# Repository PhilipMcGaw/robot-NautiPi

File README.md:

# robot-NautiPi

NautiPi is the physical hardware and embedded-project repository for the robot projects. It contains electronics, PCB and KiCad work, Arduino projects, component records, mechanical references, photographs, and retained historical hardware material.

## Robots project

Cross-project architecture, engineering rationale, significant decisions, reusable guidance, and the overall roadmap are maintained in [Chartroom](https://chartroom.philipmcgaw.com/).

NautiPi works alongside the other current project repositories:

- [Chartroom](https://chartroom.philipmcgaw.com/) — central engineering knowledge base and cross-project documentation.
- [CuttleOS](https://github.com/PhilipMcGaw/robot-CuttleOS) — robot-side software, including Cockpit, Control, and Datalogger.
- [SquidLink](https://github.com/PhilipMcGaw/robot-SquidLink) — independent ROS 2/Gazebo simulation and integration-test environment.

The repositories are separate and connected by documented interfaces. NautiPi is the source of truth for the physical hardware design record; it is not the source of truth for software implementation or simulation behaviour. Chartroom records the cross-project engineering context.

The cross-repository system architecture is maintained in [Chartroom](https://chartroom.philipmcgaw.com/). NautiPi-specific physical hardware architecture is defined in [`docs/hardware-architecture.md`](docs/hardware-architecture.md).

## Documentation standard

Project-wide documentation conventions are defined by the [Robots Project Documentation Standard](https://chartroom.philipmcgaw.com/development/documentation-standard/), maintained in Chartroom. NautiPi follows that standard and does not maintain a separate copy of the project-wide documentation rules.

## Repository layout

### ROV hardware

- [`ROV - Conductivity Temperature and Depth Transducer/`](<ROV - Conductivity Temperature and Depth Transducer/README.md>) — conductivity, temperature, and depth transducer design and embedded-project material.
- [`ROV - Light Module/`](<ROV - Light Module/README.md>) — ROV lighting electronics and embedded-project material.
- [`ROV - Main Body/`](<ROV - Main Body/README.md>) — main-body hardware archive, including PCB designs, component records, mechanical references, and historical integration material.
- [`ROV - Navigator/`](<ROV - Navigator/README.md>) — Navigator PCB, schematics, power management, status LED, leak detection, and shared KiCad resources.

### K9 hardware

- [`K9 - Main Body/`](<K9 - Main Body/README.md>) — K9 main-body hardware designs, body-control modules, motor-driver material, and project references.

### Testbot hardware

- [`TestBot - Main Body/`](<TestBot - Main Body/README.md>) — physical Testbot CAD, wiring, build notes, photographs, and validation evidence.

### MarsBot hardware and research

- [`MarsBot - Main Body/`](<MarsBot - Main Body/README.md>) — retained MarsBot main-body material and long-horizon rover-development research and roadmap work.

### Other retained material

- [`Remote Sensors/`](<Remote Sensors/README.md>) — retained remote-sensor project material.
- [`Traffic Light/`](<Traffic Light/README.md>) — historical traffic-light project photographs and reference material.

## Current status

NautiPi contains a mixture of current design work, development material, and historical project records. The presence of a design file, firmware, photograph, or other project artefact does not establish that the associated hardware is currently manufactured, assembled, commissioned, calibrated, or integrated.

Hardware assembly, electrical commissioning, calibration, environmental testing, and robot integration are separate engineering activities and require their own evidence.

The ROV hardware projects are not currently represented as production-validated by this repository unless explicit validation evidence is recorded.

## Relationship to software and simulation

CuttleOS is the current software architecture and runtime boundary. SquidLink is the current simulation and integration-test boundary. Historical software notes retained in NautiPi must not be treated as authoritative when they conflict with those repositories.

Hardware references in NautiPi do not, by themselves, authorise a Control allocation, GPIO assignment, RS-485 mapping, or production wiring arrangement. Such allocations must be established by the current engineering and software interface documentation.

## Documentation

For cross-project documentation and engineering rationale, see [Chartroom](https://chartroom.philipmcgaw.com/).

Each substantial hardware project should have a local `README.md` describing its purpose, contents, current status, and relationship to the wider system.

## People who have helped

- Philip 'Skippy' McGaw - <philip@mcgaw.eu> - [philipmcgaw.com](https://philipmcgaw.com)
- Tamarisk 'NotQuiteHere' McGaw - <tamarisk@mcgaw.eu> - [tamarisk.it](https://tamarisk.it)
- Bob 'thinkl33t' Clough - <bob@clough.me> - [thinkl33t.co.uk](https://thinkl33t.co.uk)

## Licence

The repository uses separate licences for project software and documentation, and for hardware design material. See [`LICENSES.md`](LICENSES.md) for the authoritative licensing map and the complete licence texts.

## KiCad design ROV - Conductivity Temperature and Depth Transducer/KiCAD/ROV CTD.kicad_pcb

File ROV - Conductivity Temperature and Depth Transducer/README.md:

# ROV Conductivity, Temperature, and Depth Transducer

This folder contains the KiCad design files, reference material, and embedded-project material for the ROV conductivity, temperature, and depth transducer.

## Contents

- `KiCAD/` — schematics, PCB layouts, project files, generated documents, and component resources.
- `Software/` — Arduino and PlatformIO firmware experiments and supporting libraries.

## Interface baseline

The shared node design target is **12–18 VDC nominal**, with a **24 VDC maximum
design input**. The planned field interface is Modbus RTU over RS-485 at 115200 8N1;
500 kbit/s remains optional pending complete harness and populated-bus testing.

## Development focus

The Light Module is currently the definitive playground and reference implementation for the shared ATtiny node framework. CTD firmware work is deferred while the Light Module commissioning, bus, and thermal behaviour are developed.

## Connector roles

- `J6` is the UPDI programming/diagnostic interface.
- `J7` is the external interface to the robot.
- `J2` plugs into `J3`, and `J4` plugs into `J5`, forming the CTD board stack.
## Temperature and TDS measurement

The CTD NTC is connected via `J1`, exposed to the water, and is intended to directly measure water
temperature. This temperature measurement forms part of the calculation used to
derive total dissolved solids (TDS); it is not primarily a board thermal-protection
sensor.
## Current status

The design and reference material are retained for continued development and
review. Assembly, electrical commissioning, sensor calibration, and integration
with the ROV are not recorded as complete here.

## Sources and related projects

- [OpenCTD](https://oceanographyforeveryone.com/)
- [OpenCTD on GitHub](https://github.com/OceanographyforEveryone/OpenCTD)
- [Conduino](https://github.com/feslab/conduino)
- [OpenCTD with Conduino](https://github.com/kpdangelo/OpenCTDwithConduino)
- [KiCad](https://www.kicad.org/) — PCB design software.

## Licensing

See the parent [NautiPi README](../README.md) and [licensing map](../LICENSES.md).
Hardware design files are covered by CERN-OHL-S 2.0; project software,
documentation, and reference material are covered by CC BY-NC-SA 4.0, subject to
any separate third-party notices.
## Further reading

- [jwlauer/CTD](https://github.com/jwlauer/CTD) - MS5803, NTC, pseudo-AC conductivity measurement, and calibration examples.
- [CTDizzle](https://github.com/IanTBlack/CTDizzle) - Arduino CTD construction, waterproofing, logging, and calibration.
- [OpenCTD](https://github.com/OceanographyforEveryone/OpenCTD) - Open CTD construction, calibration, and field deployment reference.
- [OpenCTD research paper](https://tos.org/oceanography/article/the-openctd-a-low-cost-open-source-ctd-for-collecting-baseline-oceanographic-data-in-coastal-waters) - Architecture and field-use background.
- [Open-source four-pole EC/CTD validation study](https://research.fs.usda.gov/treesearch/66053) - Four-electrode measurement and validation methods.
- [Cost-efficient oceanographic CTD study](https://pmc.ncbi.nlm.nih.gov/articles/PMC11207868/) - Pressure housing and deeper-water design considerations.

## Transducer modularity

The CTD intentionally combines conductivity, temperature, and pressure because they form one coherent measurement system. Temperature compensates conductivity, pressure provides depth, and the three measurements support derived salinity and density.

Other sensing functions should normally be separate RS-485/Modbus transducers using the shared Arduino hardware and firmware framework. This includes optical absorbance, turbidity, pH, dissolved oxygen, and ORP modules.
## PCB function identification

All new devices based on the Light/CTD controller shall include a resistor network on `A3/D3`. Existing legacy boards may remain exceptions until their hardware is revised.

The shared Arduino node design uses a resistor network on `A3/D3` to identify the function of the populated PCB. Firmware reads this analogue function ID during startup, selects the compatible profile, and can reject an incompatible firmware image by entering a safe diagnostic state.

This hardware function ID is separate from the robot-local Modbus address stored in EEPROM. The same firmware framework can therefore be reused across modular node types while preserving explicit hardware/firmware compatibility checks.
The initial function-code allocation is Function 1 for Light and Function 2 for CTD; Functions 3-8 are reserved. The resistor values and ADC bands shall be validated against supply variation, component tolerance, noise, and input leakage.

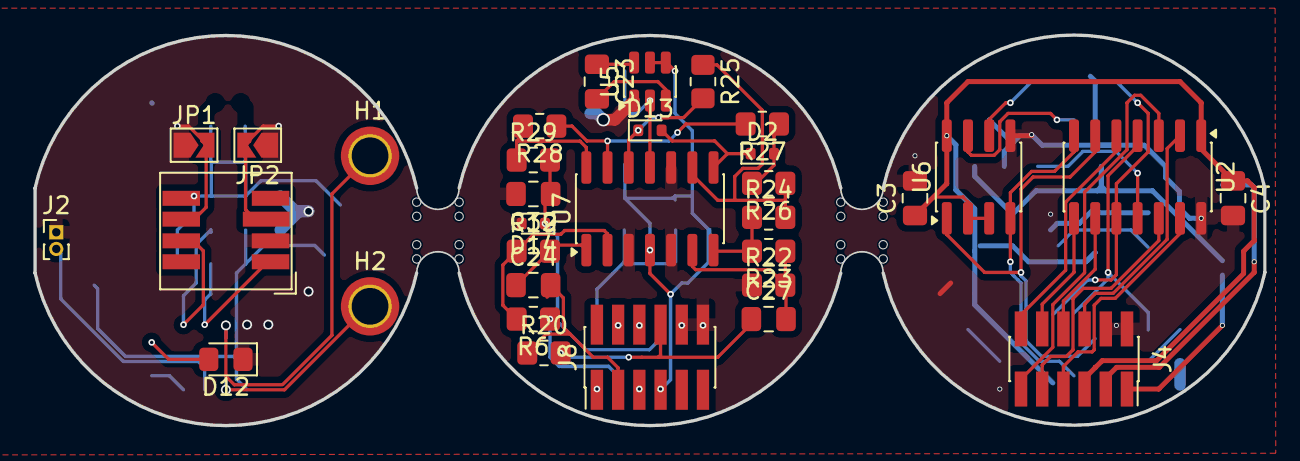
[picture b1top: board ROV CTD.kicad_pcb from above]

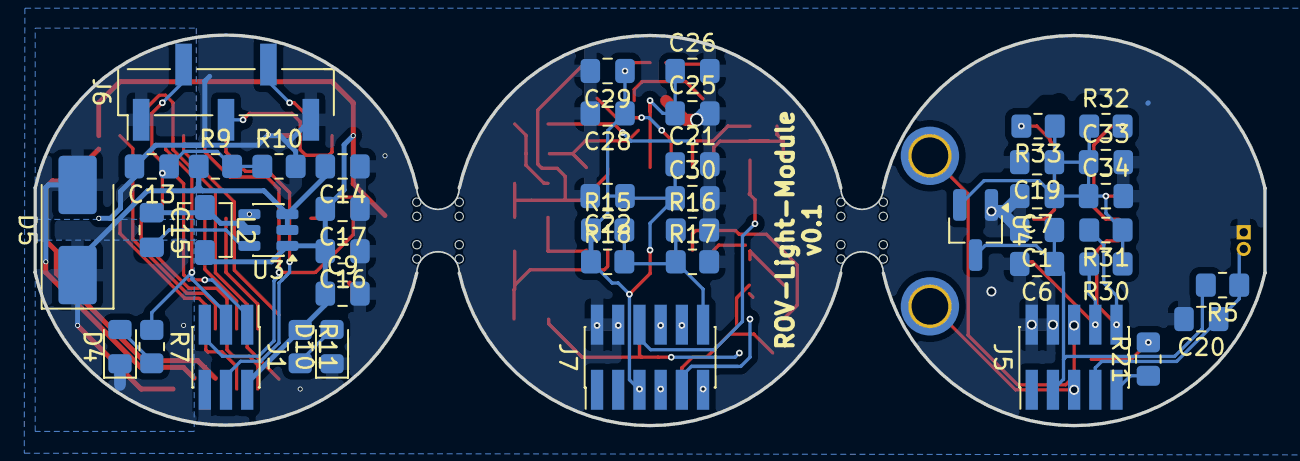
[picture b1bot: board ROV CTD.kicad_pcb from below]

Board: 2 copper layers, 73.7 x 23.4 mm, 77 parts (44 on the bottom side), 56 nets.

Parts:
C1, C7, C13, C15, C20, C22, C26, C29, C30, C33: 100nF; C_0805_2012Metric_Pad1.18x1.45mm_HandSolder
C3, C4: 10pF; C_0805_2012Metric_Pad1.18x1.45mm_HandSolder
C6, C19, C34: 10nF; C_0805_2012Metric_Pad1.18x1.45mm_HandSolder
C9: 47uF; C_0805_2012Metric_Pad1.18x1.45mm_HandSolder
C14, C21, C25: 10uF; C_0805_2012Metric_Pad1.18x1.45mm_HandSolder
C16, C17: 22uF; C_0805_2012Metric_Pad1.18x1.45mm_HandSolder
C23: 100uF; C_0805_2012Metric_Pad1.18x1.45mm_HandSolder
C24, C27: 1uF; C_0805_2012Metric_Pad1.18x1.45mm_HandSolder
C28: 4.7uF; C_0805_2012Metric_Pad1.18x1.45mm_HandSolder
C32: 20pF; C_0805_2012Metric_Pad1.18x1.45mm_HandSolder
D2, D13, D14: 1N4148WT; D_SOD-523
D4: Status; LED_0805_2012Metric_Pad1.15x1.40mm_HandSolder
D5: CZRB5370B-HF; D_SMB_Handsoldering
D10: Power; LED_0805_2012Metric_Pad1.15x1.40mm_HandSolder
D12: Status_Led; LED_0805_2012Metric_Pad1.15x1.40mm_HandSolder
H1, H2: Conductivity M2; MountingHole_2.2mm_M2_ISO7380_Pad_TopBottom
J1: AVR UPDI Header; PinHeader_2x03_P1.27mm_Vertical_SMD
J2: Temp; PinHeader_1x02_P1.00mm_Vertical
J4: Conn_02x06_Odd_Even; PinSocket_2x06_P1.27mm_Vertical_SMD
J5: Conn_02x05_Odd_Even; PinHeader_2x05_P1.27mm_Vertical_SMD
J6: Main In; PinHeader_1x05_P2.54mm_Vertical_SMD_Pin1Left
J7, J8: Conn_02x06_Odd_Even; PinHeader_2x06_P1.27mm_Vertical_SMD
JP1, JP2: RX; SolderJumper-2_P1.3mm_Open_TrianglePad1.0x1.5mm
L2: 4.7uH; L_Vishay_IHLP-1212
M1: MS5803-14BA
R5, R29, R32, R33: 10k; R_0805_2012Metric_Pad1.20x1.40mm_HandSolder
R6, R9: 51k; R_0805_2012Metric_Pad1.20x1.40mm_HandSolder
R7: 520; R_0805_2012Metric_Pad1.20x1.40mm_HandSolder
R10: 12k; R_0805_2012Metric_Pad1.20x1.40mm_HandSolder
R11, R16, R17, R18: 470; R_0805_2012Metric_Pad1.20x1.40mm_HandSolder
R15: 4k7; R_0805_2012Metric_Pad1.20x1.40mm_HandSolder
R19: 2k; R_0805_2012Metric_Pad1.20x1.40mm_HandSolder
R20, R21: 1k; R_0805_2012Metric_Pad1.20x1.40mm_HandSolder
R22: 1M; R_0805_2012Metric_Pad1.20x1.40mm_HandSolder
R23: 820; R_0805_2012Metric_Pad1.20x1.40mm_HandSolder
R24, R25, R26, R27, R28: 36k; R_0805_2012Metric_Pad1.20x1.40mm_HandSolder
R30, R31: 2k2; R_0805_2012Metric_Pad1.20x1.40mm_HandSolder
U2: ATtiny1614-Arduino; SOIC-14_3.9x8.7mm_P1.27mm
U3: AP63205WU; TSOT-23-6
U4: RT9166/A; SOT-23_Handsoldering
U5: LM2664; SOT-23-6
U6: MAX13487E; SOIC-8_3.9x4.9mm_P1.27mm
U7: LMV324; SOIC-14_3.9x8.7mm_P1.27mm

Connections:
+3V3: C7.1, C19.1, C33.1, C34.1, M1.5 (VDD), R30.1, R31.1, R32.1, R33.1, U4.2 (OUT)
+5V: C3.1, C4.1, C9.1, C16.2, C17.2, J1.2, J4.5, L2.2, R11.1, U2.1 (VCC), U3.1 (FB), U6.2 (~RE), U6.3 (~SHDN), U6.8 (VCC)
+5V_Bot: C1.1, C6.1, J5.3, R5.2, U4.3 (IN)
+5V_Mid: C21.1, C22.1, C28.1, C29.1, C30.1, J7.5, J8.7, R15.1, R18.1, U5.4 (~SD), U5.5 (V+), U7.4 (V+)
-5V: C25.1, C26.1, U5.2 (Out), U7.11 (V-)
/Arduino Driver PCB/Builtin_LED: J1.3, R7.1, U2.4 (A2/D2)
/Arduino Driver PCB/Data_A: J6.4, U6.6 (A)
/Arduino Driver PCB/Data_B: J6.3, U6.7 (B)
/Arduino Driver PCB/SERIAL_RX: J1.5, U2.6 (D4/RXD), U6.1 (RO)
/Arduino Driver PCB/SERIAL_TX: J1.4, U2.7 (~D5/TXD), U6.4 (DI)
/Arduino Driver PCB/UPDI: J1.1, J6.2, U2.10 (~RESET/UPDI)
/Arduino Driver PCB/Vmeasure: C13.1, R9.2, R10.1, U2.11 (A8/D8_MOSI)
/Bot_Probe_1: H2.1 (1_1), J5.5
/Bot_Probe_2: H1.1 (1_1), J5.6
/Bot_SCL: J5.8, M1.1 (SCL/SCLK), R30.2
/Bot_SDA: J5.10, M1.7 (SDA/SDI), R31.2
/Bot_Status_LED: J5.9, R21.1
/Bot_Temp: C20.1, J2.2, J5.7, R5.1
/Function: J4.12, U2.5 (A3/D3)
/Function_Mid: J7.12, R15.2, R16.1, R17.1, R18.2
/Mid_Probe_1: C24.2, J8.3, R20.1
/Mid_Probe_2: C27.1, J8.8, R20.2
/Mid_SCL: J7.8, J8.6
/Mid_SDA: J7.10, J8.4
/Mid_Status_LED: J7.11, J8.1
/Mid_TDS: C32.1, D14.1 (K), J7.6, R29.2
/Mid_TDS_OSC: J7.9, R6.1
/Mid_Temp: J7.7, J8.5
/Pressure Transducer/AD/CS: JP2.2 (B), M1.3 (AD/CS), R33.2
/Pressure Transducer/PS: JP1.2 (B), M1.6 (PS), R32.2
/SCL: J4.8, U2.9 (~A7/D7_SCL)
/SDA: J4.10, U2.8 (~A6/D6_SDA)
/STATUS_LED: J4.11, U2.3 (~A1/D1)
/Top_TDS: J4.6, U2.2 (~A0/D0)
/Top_TDS_OSC: J4.9, U2.12 (A9/D9_MISO)
/Top_Temp: J4.7, U2.13 (~A10/D10_SCK)
GND: C1.2, C3.2, C4.2, C6.2, C7.2, C9.2, C13.2, C14.1, C16.1, C17.1, C19.2, C20.2, C21.2, C22.2, C25.2, C26.2, C28.2, C29.2, C30.2, C32.2, C33.2, C34.2, D4.1 (K), D10.1 (K), D12.1 (K), D14.2 (A), J1.6, J2.1, J4.2, J4.4, J5.2, J5.4, J6.5, J7.2, J7.4, J8.10, J8.12, JP1.1 (A), JP2.1 (A), M1.2 (GND), R10.2, R16.2, R17.2, R22.1, U2.14 (GND), U3.4 (GND), U4.1 (GND), U5.1 (GND), U6.5 (GND), U7.3 (+), U7.5 (+), U7.10 (+)
unnamed: C24.1, R19.2, U7.1
unnamed: D2.2 (A), R26.2, R27.1
unnamed: D4.2 (A), R7.2
unnamed: D10.2 (A), R11.2
unnamed: D12.2 (A), R21.2
unnamed: D2.1 (K), D13.2 (A), U7.8
unnamed: D13.1 (K), R25.2, U7.12 (+)
unnamed: R23.2, R24.1, U7.7
unnamed: R28.2, R29.1, U7.14
unnamed: C15.2, U3.6 (BST)
unnamed: C15.1, L2.1, U3.5 (SW)
unnamed: C23.1, U5.6 (C_{FLY+})
unnamed: C23.2, U5.3 (C_{FLY-})
unnamed: R6.2, R19.1, U7.2 (-)
unnamed: C27.2, R22.2, R23.1, U7.6 (-)
unnamed: R24.2, R25.1, R26.1, U7.9 (-)
unnamed: R27.2, R28.1, U7.13 (-)
V_Supply: D5.2 (A), J4.3, J6.1
V_in: C14.2, D5.1 (K), J4.1, R9.1, U3.2 (EN), U3.3 (IN)

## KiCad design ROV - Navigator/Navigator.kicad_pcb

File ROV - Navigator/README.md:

# ROV Navigator

The Navigator directory contains the KiCad design material for the ROV Navigator hardware.

## Contents

- `Navigator.kicad_pro` — KiCad project file.
- `Navigator.kicad_sch` — main Navigator schematic.
- `Navigator.kicad_pcb` — Navigator PCB layout.
- `Power Managment.kicad_sch` — power-management schematic retained under its existing filename.
- `Status LEDs.kicad_sch` — status LED schematic.
- `leak detection.kicad_sch` — leak-detection schematic.
- `common/` — shared Navigator design resources.
- `fp-lib-table` — KiCad footprint library configuration.
- `sym-lib-table` — KiCad symbol library configuration.

## Current status

This directory is a hardware design record. The presence of KiCad project files does not, by itself, establish that the board has been manufactured, assembled, electrically commissioned, calibrated, or integrated with the current ROV software.

No production-validation claim is made here without explicit test evidence.

The current robot software architecture is maintained in CuttleOS, while simulation and integration testing are maintained in SquidLink. Hardware interfaces recorded here should therefore be treated as design information unless a separate engineering record establishes the current physical allocation.

## Documentation

Project-wide documentation requirements are defined by the [Robots Project Documentation Standard](https://chartroom.philipmcgaw.com/development/documentation-standard/), maintained in Chartroom.

The parent repository [`README.md`](../README.md) and [`LICENSES.md`](../LICENSES.md) provide the wider project context and licensing information.

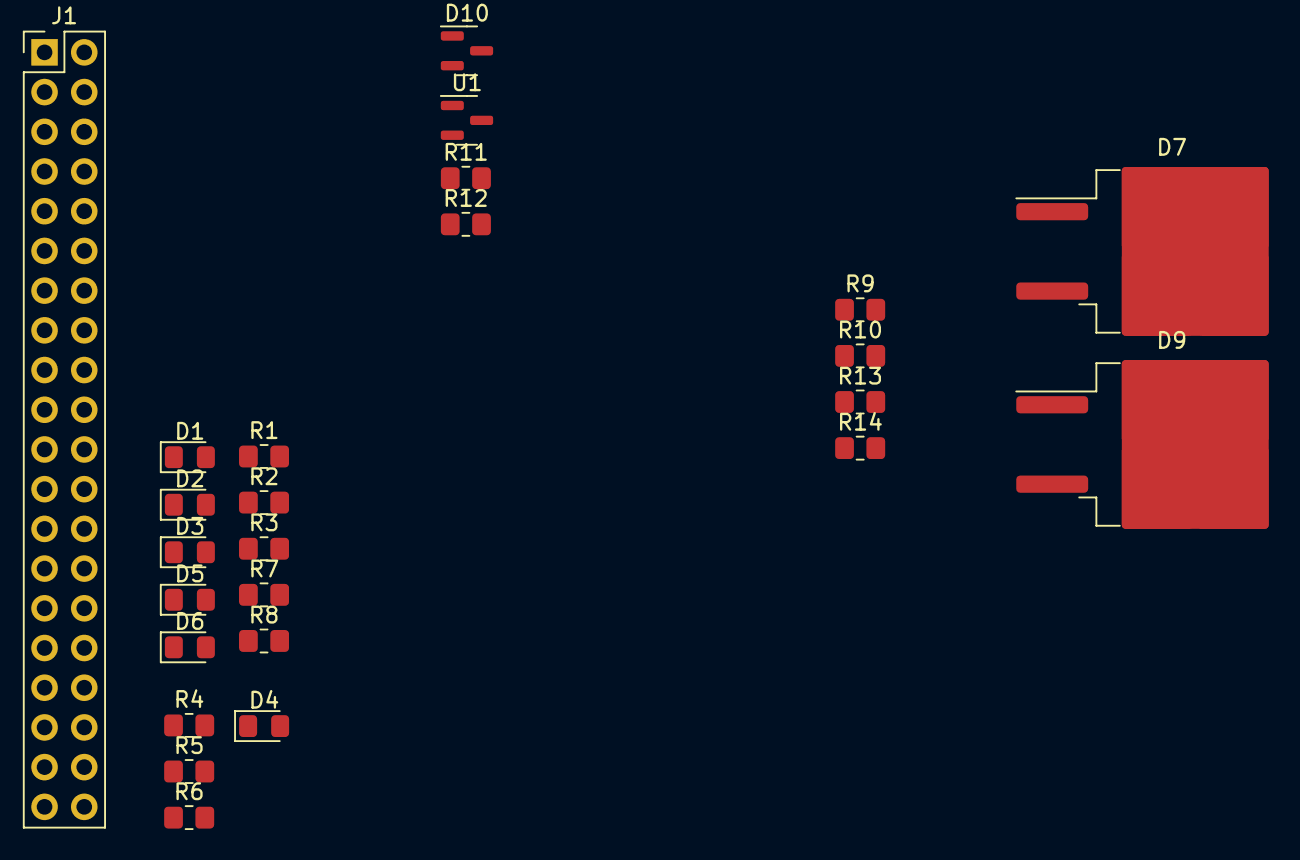
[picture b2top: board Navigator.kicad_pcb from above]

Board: 2 copper layers, 25 parts (0 on the bottom side), 20 nets, no tracks yet.

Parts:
D1: Status 1; LED_0805_2012Metric_Pad1.15x1.40mm_HandSolder
D2: Status 2; LED_0805_2012Metric_Pad1.15x1.40mm_HandSolder
D3: Status 3; LED_0805_2012Metric_Pad1.15x1.40mm_HandSolder
D4: Leak; LED_0805_2012Metric_Pad1.15x1.40mm_HandSolder
D5: 5V; LED_0805_2012Metric_Pad1.15x1.40mm_HandSolder
D6: 3V3; LED_0805_2012Metric_Pad1.15x1.40mm_HandSolder
D7, D9: VBT6045CBP-E3/4W; TO-263-2
D10: BAS40-04; SOT-23
J1: Raspberry_Pi_2_3; PinHeader_2x20_P2.54mm_Vertical
R1, R2, R3, R7, R8, R9, R10, R11, R12, R13, R14: Resistor; R_0805_2012Metric_Pad1.20x1.40mm_HandSolder
R4: 20k; R_0805_2012Metric_Pad1.20x1.40mm_HandSolder
R5: 1k; R_0805_2012Metric_Pad1.20x1.40mm_HandSolder
R6: 120; R_0805_2012Metric_Pad1.20x1.40mm_HandSolder
U1: TPS7A0508PDBZ; SOT-23

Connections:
+3V3: D10.2, R1.1, R2.1, R3.1, R4.1, R8.1, U1.2 (VO)
+5V5: R7.1, U1.3 (VI)
/LEAK_SIGNAL: J1.33 (PWM1/GPIO13), R6.1
/Power Managment/Power_1V: R9.2, R10.1
/Power Managment/Power_2V: R13.2, R14.1
/Power Managment/VOLT_IN_MON: D10.3, R11.2, R12.1
/STATUS_LED1: D1.1 (K), J1.18 (GPIO24)
/STATUS_LED2: D2.1 (K), J1.22 (GPIO25)
/STATUS_LED3: D3.1 (K), J1.23 (SCLK0/GPIO11)
GND: D4.1 (K), D5.1 (K), D6.1 (K), D10.1, J1.6 (GND), R10.2, R12.2, R14.2, U1.1 (GND)
unnamed: D1.2 (A), R1.2
unnamed: D2.2 (A), R2.2
unnamed: D3.2 (A), R3.2
unnamed: D4.2 (A), R6.2
unnamed: D5.2 (A), R7.2
unnamed: D6.2 (A), R8.2
unnamed: D7.2 (A), D9.2 (A)
unnamed: D9.1 (K), D9.3 (K), R9.1
unnamed: D7.1 (K), D7.3 (K), R13.1
unnamed: R4.2, R5.1

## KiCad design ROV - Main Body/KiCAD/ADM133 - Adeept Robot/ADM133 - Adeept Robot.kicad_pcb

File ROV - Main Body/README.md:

# ROV Main Body

This folder contains the ROV main-body hardware archive: PCB designs, component
records, mechanical references, historical project material, and integration
notes. It is part of [robot-NautiPi](../README.md), not an active software
repository.

## Contents

- `KiCAD/` — board designs, schematics, footprints, datasheets, and related design resources.
- `HighROV-Cutting-Patterns/` — retained mechanical cutting patterns and reference documents.
- `ROV/` — historical ROV photographs, reports, presentations, and reference files.
- `docs/pins.md` — historical pin and serial reference notes that require verification.
- `docs/` — integration guidance and historical engineering notes.
- `tests/` — documentation checks for the retained integration material.

## Current status

The hardware designs and reference material are retained for review and future
work. Individual board revisions, assembly, electrical commissioning, sensor
calibration, and integration with the ROV require separate evidence. Nothing in
this archive, including `docs/pins.md`, authorises a physical wiring or Control
allocation by itself.

## Interface layers

The following diagram adapts the useful structure from the former ROV overview presentation
into a reusable logical view of the robot interface layers. It replaces the
ROV-specific umbilical and topside power-management blocks with the Wi-Fi and
robot-side power boundaries used by the current architecture.

```mermaid
flowchart LR
    operator[Operator device<br/>web browser]
    network[Wi-Fi / local network]

    subgraph robot[Robot boundary]
        subgraph runtime[RPi and CuttleOS runtime]
            cockpit[Cockpit<br/>operator interface]
            nats[NATS Core<br/>application boundary]
            control[Control<br/>commands, safety, hardware drivers]
            logger[Datalogger<br/>telemetry and event recording]
            media[Media services<br/>camera and audio paths]
        end

        subgraph hardware[Hardware interface layer]
            io[GPIO / I2C / UART / USB]
            motor[Motor and load control<br/>H-bridge, PCA9685, relays]
            sensors[Sensors<br/>camera, IMU, depth, temperature, etc.]
            indicators[Indicators and audio<br/>LEDs, buzzer, speaker, microphone]
        end

        power[Robot power system<br/>battery or onboard supply<br/>regulation and protection]
        physical[Physical robot<br/>motors, thrusters, lights,<br/>manipulator, and structure]
    end

    operator -->|HTTP / WebSocket| network
    network --> cockpit
    cockpit --> nats
    nats --> control
    nats --> logger
    nats --> media
    control --> io
    control --> motor
    control --> indicators
    sensors --> io
    sensors --> media
    io --> motor
    io --> sensors
    io --> indicators
    motor --> physical
    indicators --> physical
    power --> hardware
    power --> physical
```

This is a logical interface view, not an electrical wiring schematic. See
[`docs/interface-layers.md`](docs/interface-layers.md) for the layer
responsibilities and the source-of-truth split between CuttleOS, NautiPi, and
SquidLink. Use the KiCad schematics and hardware wiring records for connector,
pin, power, and safety details.

## Active software sources

The active robot software is maintained in [robot-CuttleOS](https://github.com/PhilipMcGaw/robot-CuttleOS).
The independent simulation and integration-test environment is maintained in
[robot-SquidLink](https://github.com/PhilipMcGaw/robot-SquidLink). Their
interfaces and status documentation take precedence over the historical
software-orientation notes retained under `docs/`.

## Documentation

Start with [`docs/README.md`](docs/README.md) for the retained integration
notes. The module and board READMEs inside `KiCAD/` provide more specific
information where available. Historical research, imported reference files,
and third-party material must retain their own notices.

## Licensing

See the parent [NautiPi licensing map](../LICENSES.md). Hardware design files
are covered by CERN-OHL-S 2.0; project software, documentation, and reference
material are covered by CC BY-NC-SA 4.0, subject to any separate third-party
notices. The parent NautiPi licensing map is the source of truth for this folder.

## People who have helped

- Philip 'Skippy' McGaw - <philip@mcgaw.eu> - [philipmcgaw.com](https://philipmcgaw.com)
- Tamarisk 'NotQuiteHere' McGaw - <tamarisk@mcgaw.eu> - [tamarisk.it](https://tamarisk.it)
- Bob 'thinkl33t' Clough - <bob@clough.me> - [thinkl33t.co.uk](https://thinkl33t.co.uk)

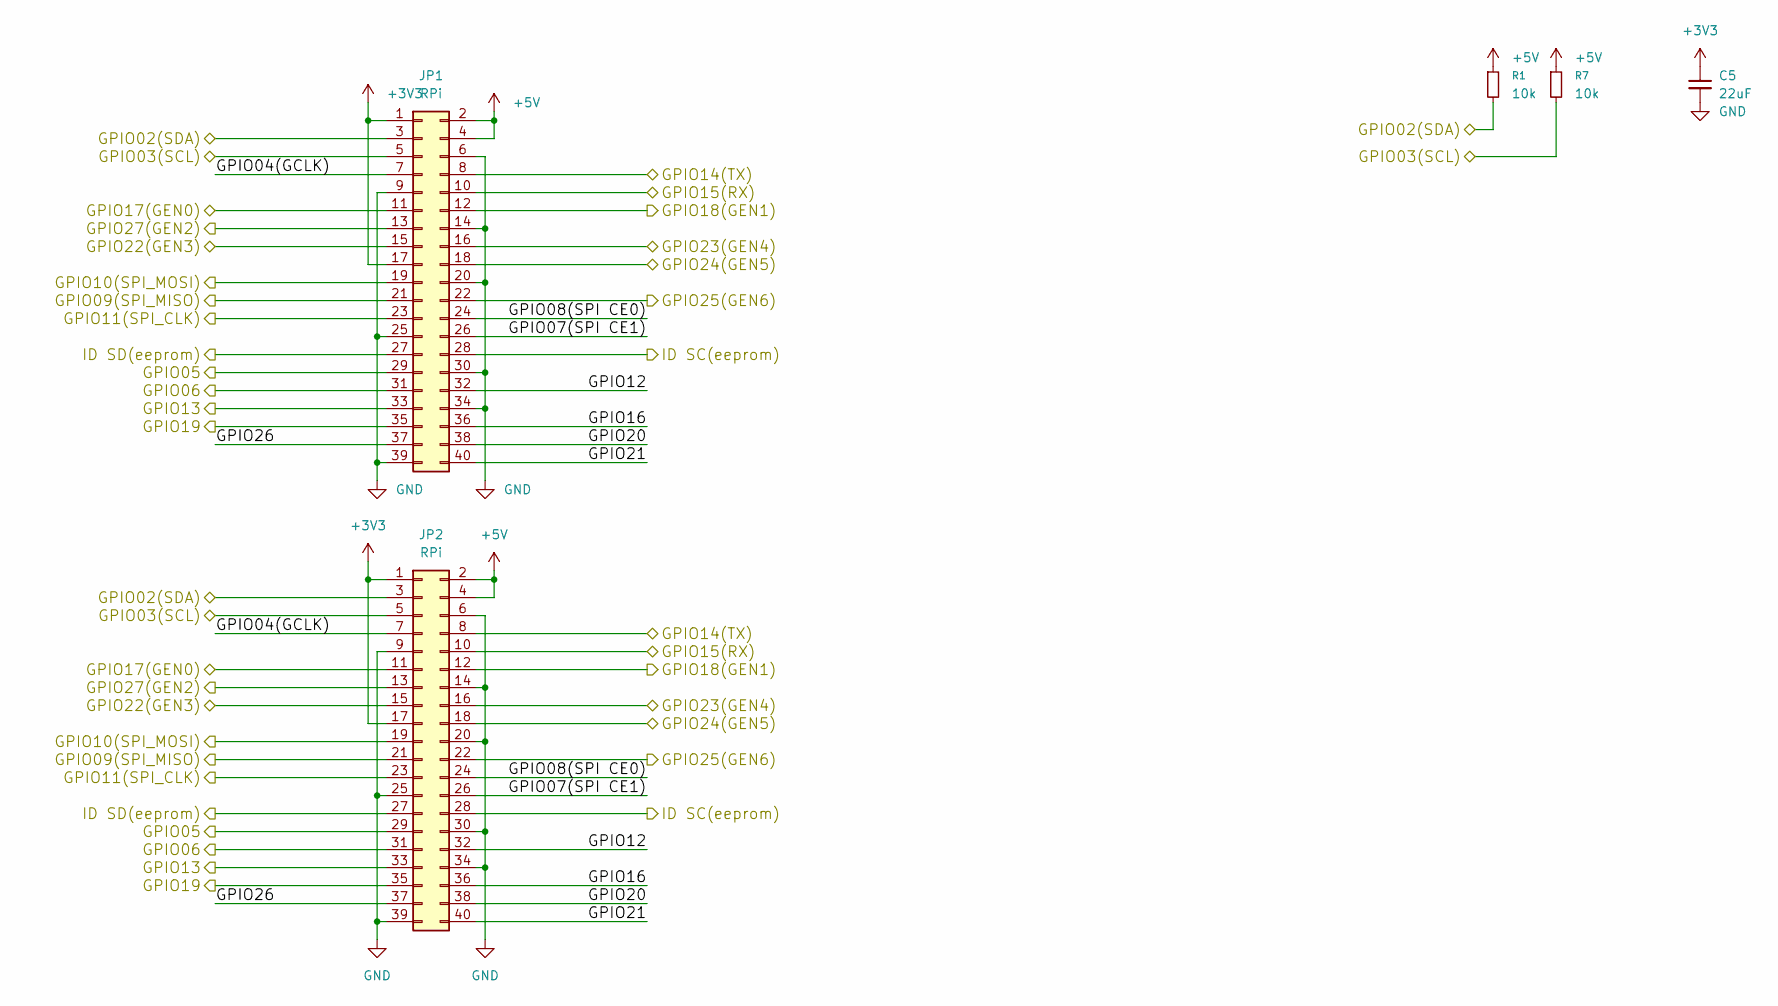
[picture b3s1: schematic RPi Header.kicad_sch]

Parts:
C5: 22uF; C_0805_2012Metric_Pad1.18x1.45mm_HandSolder
JP1: RPi; PinSocket_2x20_P2.54mm_Vertical
JP2: RPi; PinHeader_2x20_P2.54mm_Vertical
R1, R7: 10k; R_0805_2012Metric_Pad1.20x1.40mm_HandSolder

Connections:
+3V3: C5.1, JP1.1, JP1.17, JP2.1, JP2.17; also elsewhere on the board
/Analogue Interface/GPIO02(SDA): JP1.3, JP2.3, R1.2; also elsewhere on the board
/Analogue Interface/GPIO03(SCL): JP1.5, JP2.5, R7.2; also elsewhere on the board
/Buzzer/GPIO18(GEN1): JP1.12, JP2.12; also elsewhere on the board
/Neopixle Interface/GPIO10(SPI_MOSI): JP1.19, JP2.19; also elsewhere on the board
/RPi Header/GPIO04(GCLK): JP1.7, JP2.7
/RPi Header/GPIO05: JP1.29, JP2.29; also elsewhere on the board
/RPi Header/GPIO06: JP1.31, JP2.31; also elsewhere on the board
/RPi Header/GPIO07(SPI CE1): JP1.26, JP2.26
/RPi Header/GPIO08(SPI CE0): JP1.24, JP2.24
/RPi Header/GPIO09(SPI_MISO): JP1.21, JP2.21; also elsewhere on the board
/RPi Header/GPIO11(SPI_CLK): JP1.23, JP2.23; also elsewhere on the board
/RPi Header/GPIO12: JP1.32, JP2.32
/RPi Header/GPIO13: JP1.33, JP2.33; also elsewhere on the board
/RPi Header/GPIO14(TX): JP1.8, JP2.8; also elsewhere on the board
/RPi Header/GPIO15(RX): JP1.10, JP2.10; also elsewhere on the board
/RPi Header/GPIO16: JP1.36, JP2.36
/RPi Header/GPIO17(GEN0): JP1.11, JP2.11; also elsewhere on the board
/RPi Header/GPIO19: JP1.35, JP2.35; also elsewhere on the board
/RPi Header/GPIO20: JP1.38, JP2.38
/RPi Header/GPIO21: JP1.40, JP2.40
/RPi Header/GPIO22(GEN3): JP1.15, JP2.15; also elsewhere on the board
/RPi Header/GPIO23(GEN4): JP1.16, JP2.16; also elsewhere on the board
/RPi Header/GPIO24(GEN5): JP1.18, JP2.18; also elsewhere on the board
/RPi Header/GPIO25(GEN6): JP1.22, JP2.22; also elsewhere on the board
/RPi Header/GPIO26: JP1.37, JP2.37
/RPi Header/GPIO27(GEN2): JP1.13, JP2.13; also elsewhere on the board
/RPi Header/ID SC(eeprom): JP1.28, JP2.28; also elsewhere on the board
/RPi Header/ID SD(eeprom): JP1.27, JP2.27; also elsewhere on the board

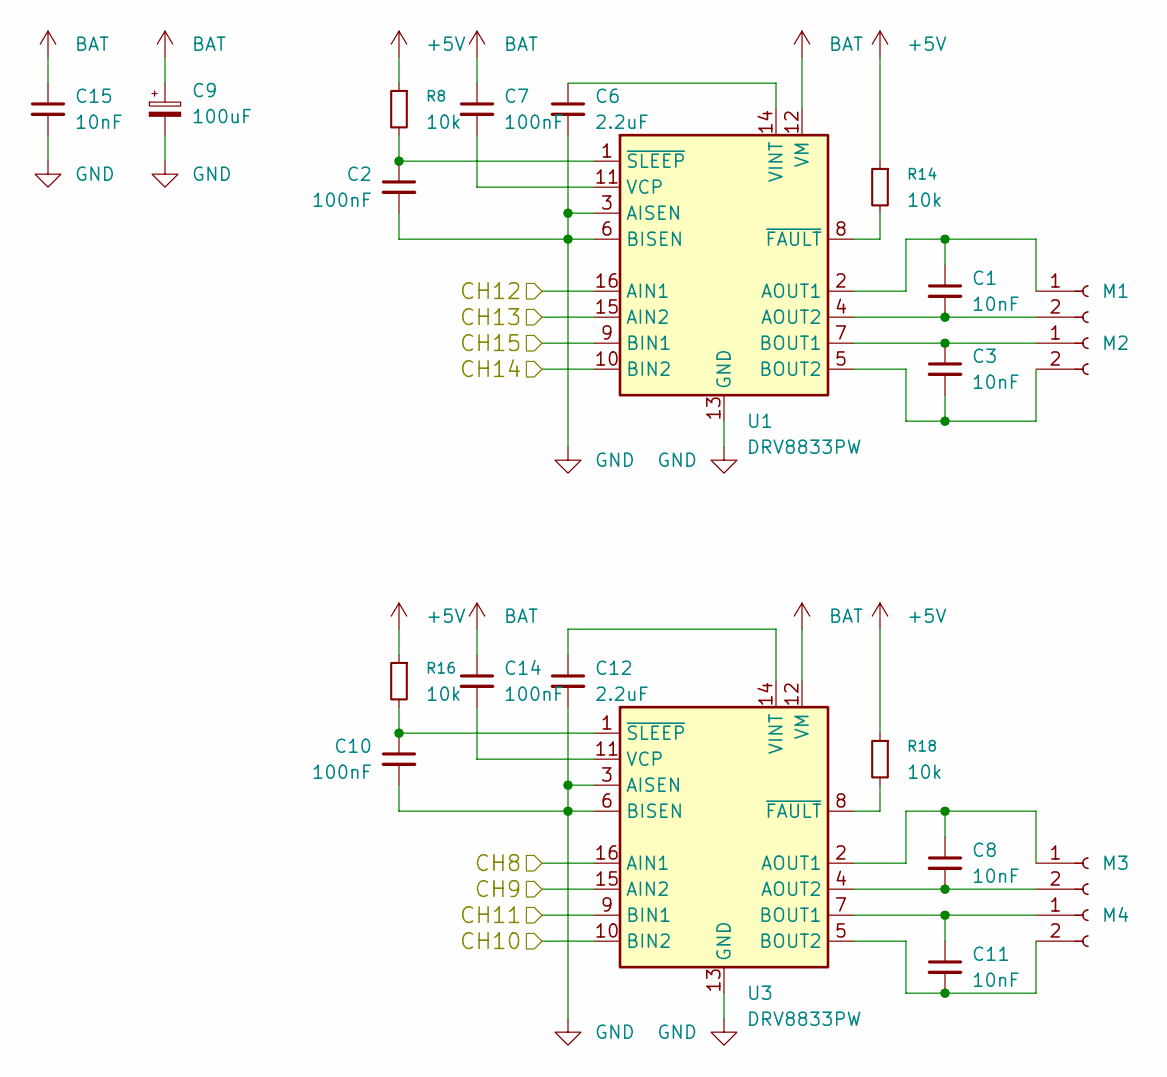
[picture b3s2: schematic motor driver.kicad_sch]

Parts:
C1, C3, C8, C11, C15: 10nF; C_0805_2012Metric_Pad1.18x1.45mm_HandSolder
C2, C7, C10, C14: 100nF; C_0805_2012Metric_Pad1.18x1.45mm_HandSolder
C6, C12: 2.2uF; C_0805_2012Metric_Pad1.18x1.45mm_HandSolder
C9: 100uF
M1, M2, M3, M4: PinHeader_1x02_P2.54mm_Vertical
R8, R14, R16, R18: 10k; R_0805_2012Metric_Pad1.20x1.40mm_HandSolder
U1, U3: DRV8833PW; TSSOP-16_4.4x5mm_P0.65mm

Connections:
/Servo Interface/CH8: U3.16 (AIN1); also elsewhere on the board
/Servo Interface/CH9: U3.15 (AIN2); also elsewhere on the board
/Servo Interface/CH10: U3.10 (BIN2); also elsewhere on the board
/Servo Interface/CH11: U3.9 (BIN1); also elsewhere on the board
/Servo Interface/CH12: U1.16 (AIN1); also elsewhere on the board
/Servo Interface/CH13: U1.15 (AIN2); also elsewhere on the board
/Servo Interface/CH14: U1.10 (BIN2); also elsewhere on the board
/Servo Interface/CH15: U1.9 (BIN1); also elsewhere on the board
BAT: C7.1, C9.1, C14.1, C15.1, U1.12 (VM), U3.12 (VM); also elsewhere on the board
unnamed: C1.1, M1.1, U1.2 (AOUT1)
unnamed: C1.2, M1.2, U1.4 (AOUT2)
unnamed: C3.1, M2.1, U1.7 (BOUT1)
unnamed: C3.2, M2.2, U1.5 (BOUT2)
unnamed: C8.1, M3.1, U3.2 (AOUT1)
unnamed: C8.2, M3.2, U3.4 (AOUT2)
unnamed: C11.1, M4.1, U3.7 (BOUT1)
unnamed: C11.2, M4.2, U3.5 (BOUT2)
unnamed: C7.2, U1.11 (VCP)
unnamed: C6.1, U1.14 (VINT)
unnamed: R14.2, U1.8 (~FAULT)
unnamed: C2.1, R8.2, U1.1 (~SLEEP)
unnamed: C14.2, U3.11 (VCP)
unnamed: C12.1, U3.14 (VINT)
unnamed: R18.2, U3.8 (~FAULT)
unnamed: C10.1, R16.2, U3.1 (~SLEEP)

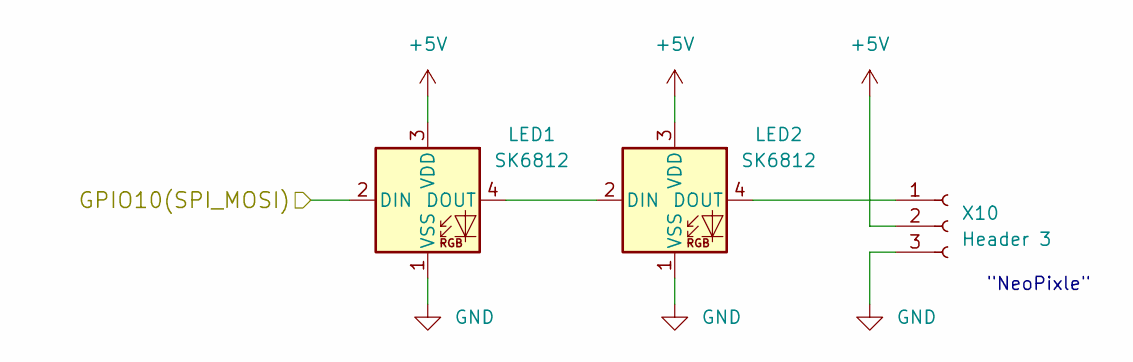
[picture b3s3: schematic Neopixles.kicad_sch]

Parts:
LED1, LED2: SK6812; LED_SK6812_PLCC4_5.0x5.0mm_P3.2mm
X10: Header 3; JST_EH_B3B-EH-A_1x03_P2.50mm_Vertical

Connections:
/Neopixle Interface/GPIO10(SPI_MOSI): LED1.2 (DIN); also elsewhere on the board
unnamed: LED1.4 (DOUT), LED2.2 (DIN)
unnamed: LED2.4 (DOUT), X10.1

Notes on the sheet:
"NeoPixle"

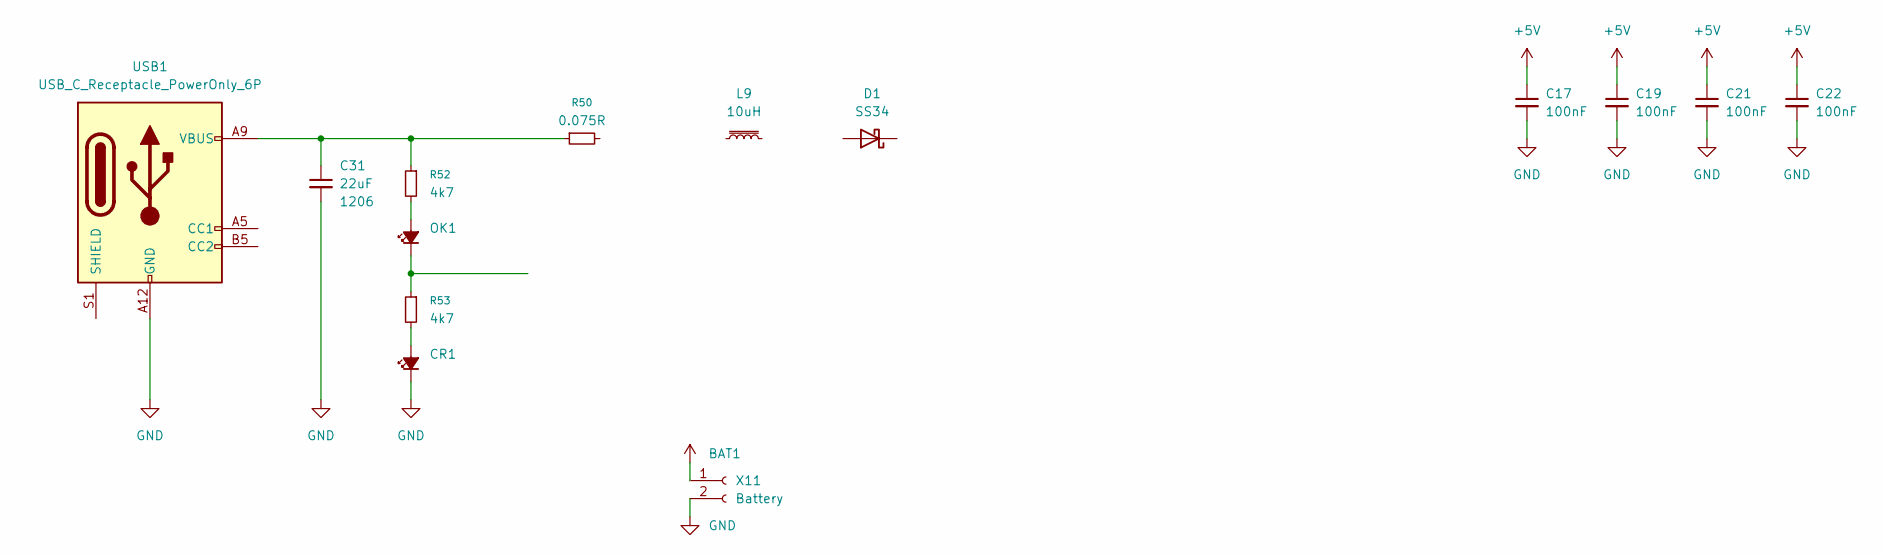
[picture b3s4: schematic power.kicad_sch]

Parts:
C17, C19, C21, C22: 100nF; C_0805_2012Metric_Pad1.18x1.45mm_HandSolder
C31: 22uF; C_1206_3216Metric_Pad1.33x1.80mm_HandSolder
CR1: LED_0805_2012Metric_Pad1.15x1.40mm_HandSolder
D1: SS34; D_SMA-SMB_Universal_Handsoldering
L9: 10uH; L_7.3x7.3_H3.5
OK1: LED_0805_2012Metric_Pad1.15x1.40mm_HandSolder
R50: 0.075R; R_2010_5025Metric_Pad1.40x2.65mm_HandSolder
R52, R53: 4k7; R_0805_2012Metric_Pad1.20x1.40mm_HandSolder
USB1: USB_C_Receptacle_PowerOnly_6P; USB_C_Receptacle_GCT_USB4125-xx-x_6P_TopMnt_Horizontal
X11: Battery; PinHeader_1x02_P2.54mm_Vertical

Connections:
BAT1: X11.1
unnamed: C31.1, R50.1, R52.1, USB1.A9 (VBUS), USB1.B9 (VBUS)
unnamed: CR1.2 (A), R53.2
unnamed: OK1.2 (A), R52.2
unnamed: OK1.1 (K), R53.1

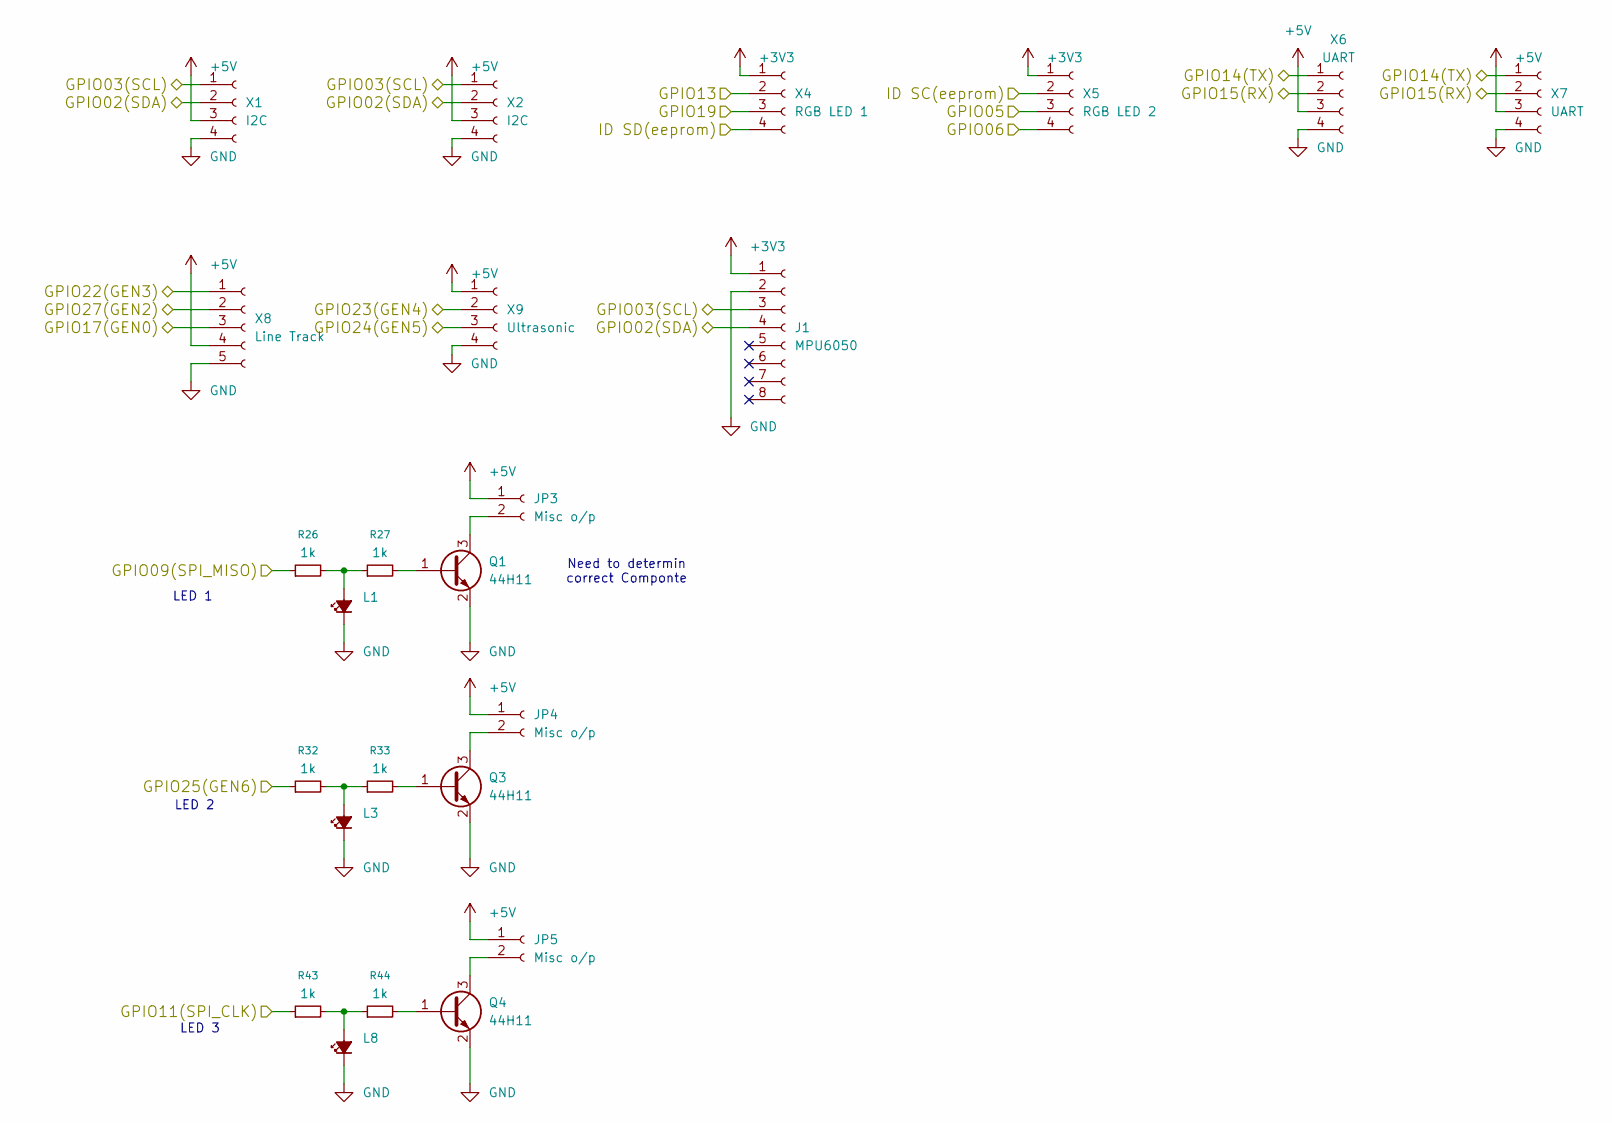
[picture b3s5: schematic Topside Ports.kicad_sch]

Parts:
J1: MPU6050; PinSocket_1x08_P2.54mm_Vertical
JP3, JP4, JP5: Misc o/p; PinHeader_1x02_P2.54mm_Vertical
L1, L3, L8: LED_0805_2012Metric_Pad1.15x1.40mm_HandSolder
Q1, Q3, Q4: 44H11; SOT-23_Handsoldering
R26, R27, R32, R33, R43, R44: 1k; R_0805_2012Metric_Pad1.20x1.40mm_HandSolder
X1, X2: I2C; JST_EH_B4B-EH-A_1x04_P2.50mm_Vertical
X4: RGB LED 1; JST_EH_B4B-EH-A_1x04_P2.50mm_Vertical
X5: RGB LED 2; JST_EH_B4B-EH-A_1x04_P2.50mm_Vertical
X6, X7: UART; JST_EH_B4B-EH-A_1x04_P2.50mm_Vertical
X8: Line Track; JST_EH_B5B-EH-A_1x05_P2.50mm_Vertical
X9: Ultrasonic; JST_EH_B4B-EH-A_1x04_P2.50mm_Vertical

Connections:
+3V3: J1.1, X4.1, X5.1; also elsewhere on the board
/Analogue Interface/GPIO02(SDA): J1.4, X1.2, X2.2; also elsewhere on the board
/Analogue Interface/GPIO03(SCL): J1.3, X1.1, X2.1; also elsewhere on the board
/RPi Header/GPIO05: X5.3; also elsewhere on the board
/RPi Header/GPIO06: X5.4; also elsewhere on the board
/RPi Header/GPIO09(SPI_MISO): R26.1; also elsewhere on the board
/RPi Header/GPIO11(SPI_CLK): R43.1; also elsewhere on the board
/RPi Header/GPIO13: X4.2; also elsewhere on the board
/RPi Header/GPIO14(TX): X6.1, X7.1; also elsewhere on the board
/RPi Header/GPIO15(RX): X6.2, X7.2; also elsewhere on the board
/RPi Header/GPIO17(GEN0): X8.3; also elsewhere on the board
/RPi Header/GPIO19: X4.3; also elsewhere on the board
/RPi Header/GPIO22(GEN3): X8.1; also elsewhere on the board
/RPi Header/GPIO23(GEN4): X9.2; also elsewhere on the board
/RPi Header/GPIO24(GEN5): X9.3; also elsewhere on the board
/RPi Header/GPIO25(GEN6): R32.1; also elsewhere on the board
/RPi Header/GPIO27(GEN2): X8.2; also elsewhere on the board
/RPi Header/ID SC(eeprom): X5.2; also elsewhere on the board
/RPi Header/ID SD(eeprom): X4.4; also elsewhere on the board
unnamed: JP3.2, Q1.3 (C)
unnamed: JP4.2, Q3.3 (C)
unnamed: JP5.2, Q4.3 (C)
unnamed: L1.2 (A), R26.2, R27.1
unnamed: L3.2 (A), R32.2, R33.1
unnamed: L8.2 (A), R43.2, R44.1
unnamed: Q1.1 (B), R27.2
unnamed: Q3.1 (B), R33.2
unnamed: Q4.1 (B), R44.2

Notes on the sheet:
LED 3
LED 1
Need to determin correct Componte
LED 2

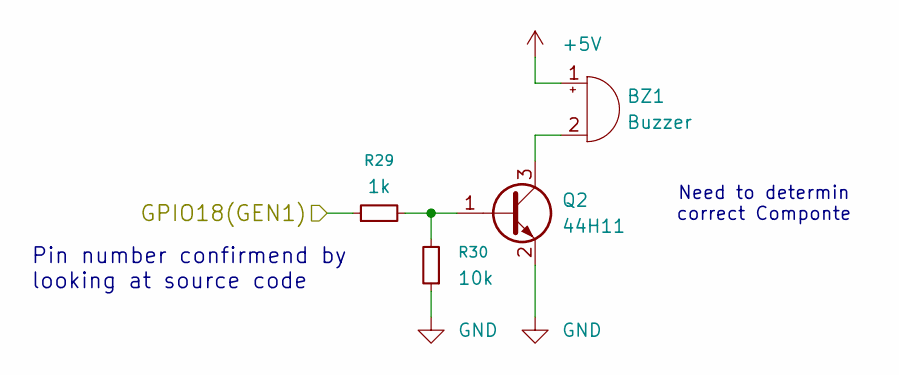
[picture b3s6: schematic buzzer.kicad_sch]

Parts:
BZ1: Buzzer; Buzzer_Mallory_AST1240MLQ
Q2: 44H11; SOT-23_Handsoldering
R29: 1k; R_0805_2012Metric_Pad1.20x1.40mm_HandSolder
R30: 10k; R_0805_2012Metric_Pad1.20x1.40mm_HandSolder

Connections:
/Buzzer/GPIO18(GEN1): R29.1; also elsewhere on the board
unnamed: BZ1.2 (-), Q2.3 (C)
unnamed: Q2.1 (B), R29.2, R30.2

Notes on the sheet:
Need to determin correct Componte
Pin number confirmend by looking at source code

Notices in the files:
README.md:
Software, documentation, and reference material: CC BY-NC-SA 4.0
Hardware: CERN-OHL-S 2.0
ROV - Main Body/KiCAD/TopSide/OpenROV Topside Interface 2.6A.kicad_pcb:
This work is released under the
Creative Commons Attribution-
